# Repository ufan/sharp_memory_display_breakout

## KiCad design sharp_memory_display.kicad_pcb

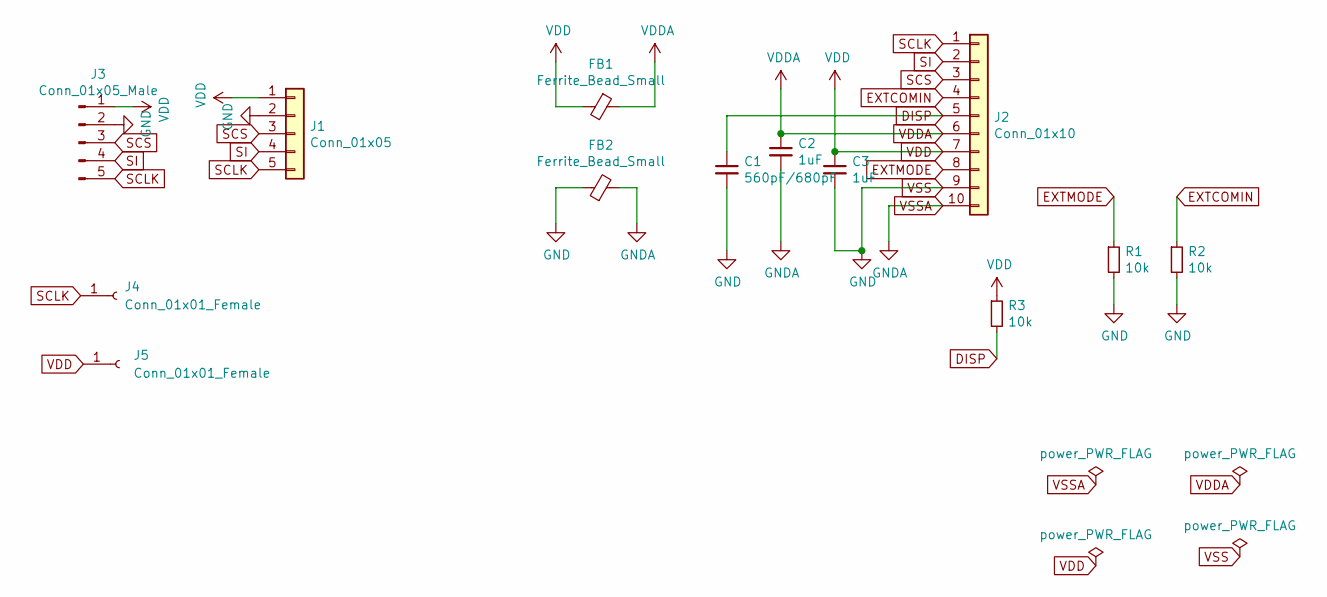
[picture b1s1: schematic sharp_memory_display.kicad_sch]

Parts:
C1: 560pF/680pF; C_0603_1608Metric_Pad1.08x0.95mm_HandSolder; LCSC C84721
C2, C3: 1uF; C_0603_1608Metric_Pad1.08x0.95mm_HandSolder; LCSC C15849
FB1, FB2: Ferrite_Bead_Small; R_0805_2012Metric_Pad1.20x1.40mm_HandSolder; LCSC C1017
J1: Conn_01x05; PinSocket_1x05_P2.54mm_Vertical
J2: Conn_01x10; Hirose_FH12-10S-0.5SH_1x10-1MP_P0.50mm_Horizontal; LCSC C506791
J3: Conn_01x05_Male; JST_SH_SM05B-SRSS-TB_1x05-1MP_P1.00mm_Horizontal
J4, J5: Conn_01x01_Female; PinSocket_1x01_P2.54mm_Vertical
R1, R2, R3: 10k; R_0603_1608Metric_Pad0.98x0.95mm_HandSolder; LCSC C25804

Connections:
DISP: C1.1, J2.5, R3.2
EXTCOMIN: J2.4, R2.1
EXTMODE: J2.8, R1.1
SCLK: J1.5, J2.1, J3.5, J4.1
SCS: J1.3, J2.3, J3.3
SI: J1.4, J2.2, J3.4
VDD: C3.1, FB1.2, J1.1, J2.7, J3.1, J5.1, R3.1
VDDA: C2.1, FB1.1, J2.6
VSS: C1.2, C3.2, FB2.1, J1.2, J2.9, J3.2, R1.2, R2.2
VSSA: C2.2, FB2.2, J2.10

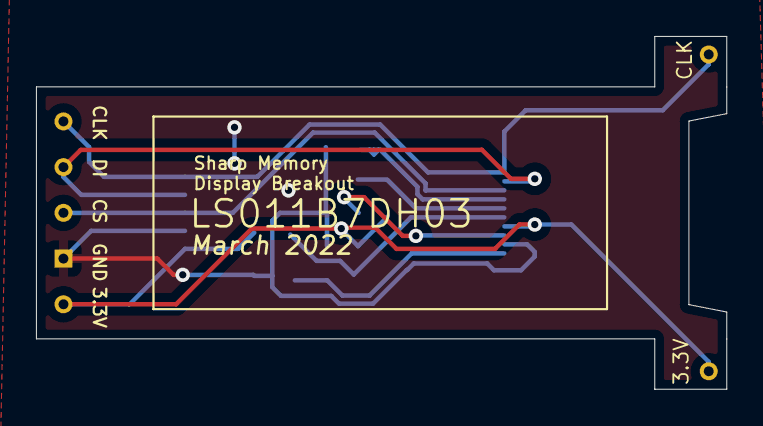
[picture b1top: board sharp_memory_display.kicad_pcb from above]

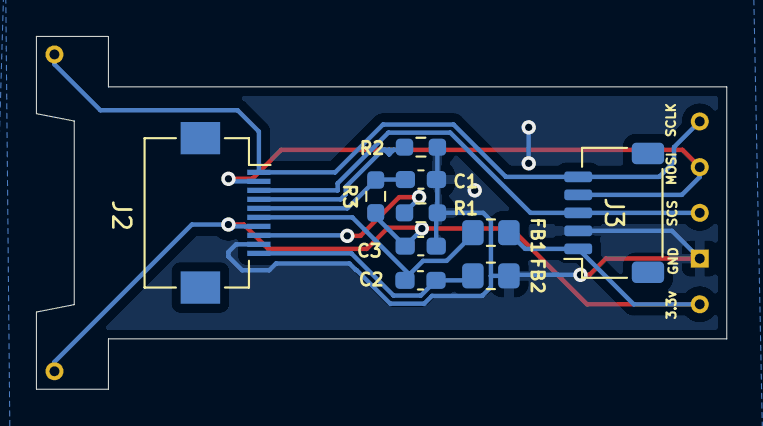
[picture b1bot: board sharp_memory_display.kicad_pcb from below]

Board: 2 copper layers, 38.4 x 19.6 mm, 13 parts (10 on the bottom side), 10 nets.

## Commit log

2022-05-26 add bom
2022-09-12 backup
2022-09-12 simplified version
2022-09-12 add zip file of simple version
2022-09-13 add two extra pint sockets
2022-09-13 add t-shape gerber
2022-09-13 update diplay panel outline in front silkmark
